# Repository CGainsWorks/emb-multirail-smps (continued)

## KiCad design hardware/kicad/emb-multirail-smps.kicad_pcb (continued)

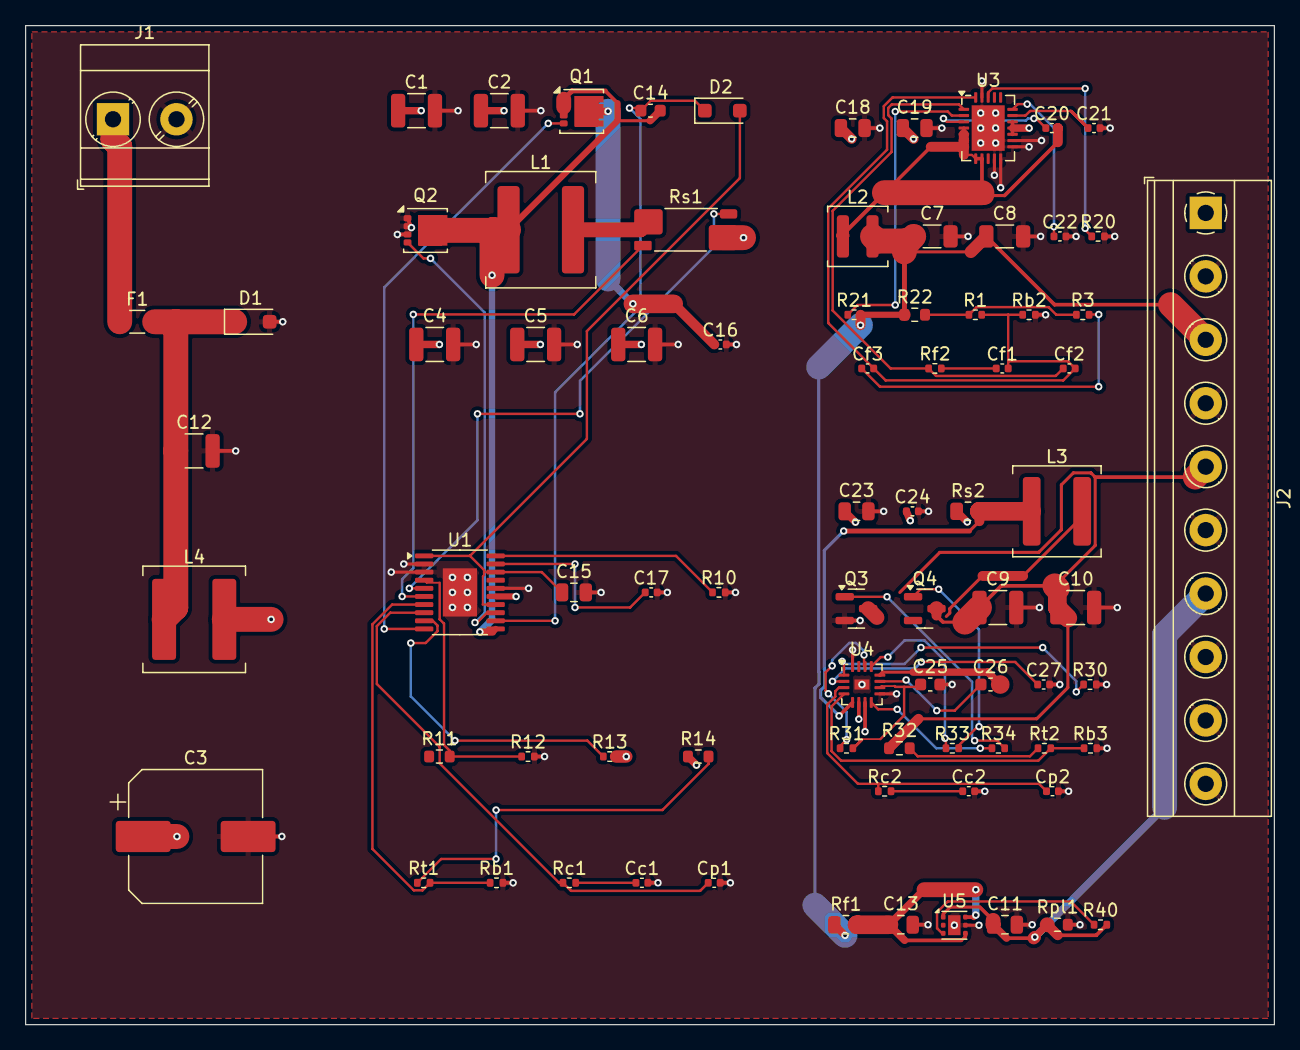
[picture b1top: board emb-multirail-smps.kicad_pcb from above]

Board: 4 copper layers, 100.0 x 80.0 mm, 79 parts (0 on the bottom side), 52 nets.

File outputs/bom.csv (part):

refs,qty,value,description,footprint,manufacturer,mpn,basis,status
J1,1,VIN 8-36V,"Input terminal block, 2 way, 5.08 mm",TerminalBlock_Phoenix:TerminalBlock_Phoenix_MKDS-3-2-5.08_1x02_P5.08mm_Horizontal,Phoenix Contact,1711725,choice,"selected, data sheet check pending"
F1,1,3A,"Fuse, 3 A slow blow, 63 V DC, 1206",Fuse:Fuse_1206_3216Metric,Eaton Bussmann,CC12H3A-TR,choice,"selected, data sheet check pending"
D1,1,SMF36A,"TVS, 36 V stand off, unidirectional, SOD-123FL. Clamps input transients and conducts on reverse polarity until F1 opens",Diode_SMD:D_SOD-123F,Littelfuse,SMF36A,choice,"selected, data sheet check pending"
C12,1,2.2uF,"Input filter shunt capacitor, connector side, 2.2 uF 100 V X7R",Capacitor_SMD:C_1210_3225Metric,Murata,GRM32ER72A225KA35L,model,"selected, data sheet check pending"
L4,1,10uH,"Differential mode input filter inductor, 10 uH",Inductor_SMD:L_Coilcraft_XAL7050-XXX,Coilcraft,XAL7050-103MEC,model,"selected, data sheet check pending"
C3,1,220uF,"Hybrid polymer aluminium 220 uF 50 V, 10 x 16.5 mm, input filter damping",Capacitor_SMD:CP_Elec_10x10.5,Panasonic,EEH-ZS1H221P,model,"selected, data sheet check pending"
C1 C2,2,10uF,"+5V buck input capacitor, 10 uF 50 V X7R 1210",Capacitor_SMD:C_1210_3225Metric,Murata,GRM32ER71H106KA12L,model,"selected, data sheet check pending"
U1,1,LTC3891EFE#PBF,"60 V synchronous buck controller, peak current mode, 0.8 V reference",Package_SO:HTSSOP-20-1EP_4.4x6.5mm_P0.65mm_EP2.74x3.86mm,Analog Devices,LTC3891EFE#PBF,datasheet,"selected, data sheet check pending"
Q1 Q2,2,CSD18543Q3A,"60 V N-channel MOSFET, high side",Package_SON:VSON-8_3.3x3.3mm_P0.65mm_NexFET,Texas Instruments,CSD18543Q3A,choice,"selected, data sheet check pending"
D2,1,PMEG6010CEH,"Bootstrap diode, 60 V Schottky. The data sheet calls for one between INTVCC and BOOST",Diode_SMD:D_SOD-123F,Nexperia,PMEG6010CEH,datasheet,"selected, data sheet check pending"
C14 C26,2,100nF,"Bootstrap capacitor, 0.1 uF 50 V",Capacitor_SMD:C_0603_1608Metric,Murata,GRM188R71H104KA93D,datasheet,"selected, data sheet check pending"
C15,1,4.7uF,INTVCC decoupling. Data sheet minimum 2.2 uF,Capacitor_SMD:C_0805_2012Metric,Murata,GRM21BR71C475KA73L,datasheet,"selected, data sheet check pending"
C16 C21 C24 Cc2,4,100nF,VIN pin bypass to SGND,Capacitor_SMD:C_0402_1005Metric,Murata,GRM155R71H104KE14D,datasheet,"selected, data sheet check pending"
C17 C20 C27,3,47nF,Soft start. tSS = CSS * 0.8 V / 10 uA = 3.8 ms,Capacitor_SMD:C_0402_1005Metric,Murata,GRM155R71C473KA01D,datasheet,"selected, data sheet check pending"
R10,1,71.5k,"Frequency set, 500 kHz",Resistor_SMD:R_0402_1005Metric,Yageo,RC0402FR-0771K5L,datasheet,"selected, data sheet check pending"
R11,1,1M,RUN divider top. Starts at about 7 V rising,Resistor_SMD:R_0603_1608Metric,Yageo,RC0603FR-071ML,datasheet,"selected, data sheet check pending"
R12,1,210k,"RUN divider bottom. 1.21 V threshold, 6.3 V at 36 V in",Resistor_SMD:R_0402_1005Metric,Yageo,RC0402FR-07210KL,datasheet,"selected, data sheet check pending"
R13 R21 R40,3,100k,PGOOD pull-up,Resistor_SMD:R_0402_1005Metric,Yageo,RC0402FR-07100KL,choice,"selected, data sheet check pending"
L1,1,6.8uH,"+5V buck inductor, 6.8 uH",Inductor_SMD:L_Coilcraft_XAL8080-XXX,Coilcraft,XAL8080-682MED,model,"selected, data sheet check pending"
Rs1,1,5m,"Current sense shunt, 5 mOhm 1 %, four terminal 2512",Resistor_SMD:R_Shunt_Vishay_WSK2512_6332Metric_T1.19mm,Vishay,WSK25125L000FEA,model,"selected, data sheet check pending"
C4 C5 C6 C9 C10,5,22uF,"+5V output capacitor, 22 uF 25 V X7R 1210",Capacitor_SMD:C_1210_3225Metric,Murata,GRM32ER71E226KE15L,model,"selected, data sheet check pending"
R14 R22 R32,3,0,Loop injection link. Fitted 0 ohm; replace with 20 ohm for a Bode measurement,Resistor_SMD:R_0603_1608Metric,Yageo,RC0603JR-070RL,choice,"selected, data sheet check pending"
Rt1,1,26.1k,+5V divider top,Resistor_SMD:R_0402_1005Metric,Yageo,RC0402FR-0726K1L,model,"selected, data sheet check pending"
Rb1 Rb3,2,4.99k,+5V divider bottom,Resistor_SMD:R_0402_1005Metric,Yageo,RC0402FR-074K99L,model,"selected, data sheet check pending"
Rc1,1,2.4k,"+5V Type II, Rc",Resistor_SMD:R_0402_1005Metric,Yageo,RC0402FR-072K4L,model,"selected, data sheet check pending"
Cc1,1,15nF,"+5V Type II, Cc",Capacitor_SMD:C_0402_1005Metric,Murata,GRM155R71H153KA12D,model,"selected, data sheet check pending"
Cp1 Cp2,2,270pF,"+5V Type II, Cp",Capacitor_SMD:C_0402_1005Metric,KEMET,C0402C271J5GACTU,model,"selected, data sheet check pending"
U3,1,TPS54317RHFR,"3 to 6 V input, 3 A synchronous buck, voltage mode, integrated FETs, 0.891 V reference",Package_DFN_QFN:QFN-24-1EP_4x5mm_P0.5mm_EP2.65x3.65mm,Texas Instruments,TPS54317RHFR,datasheet,"selected, data sheet check pending"
C18 C19 C23 C13,4,10uF,"+3V3 buck input capacitor, 10 uF 16 V X7R 0805",Capacitor_SMD:C_0805_2012Metric,Samsung,CL21B106KOQNNNE,model,"selected, data sheet check pending"
C22,1,22nF,Slow start. t = C * 0.7 V / 5 uA = 3.1 ms,Capacitor_SMD:C_0402_1005Metric,Murata,GRM155R71H223KA12D,datasheet,"selected, data sheet check pending"
R20,1,46.4k,"Frequency set, 1 MHz. f(MHz) = 51k / (R + 4.7k) gives 46.3k",Resistor_SMD:R_0402_1005Metric,Yageo,RC0402FR-0746K4L,datasheet,"selected, data sheet check pending"
L2,1,1.5uH,"+3V3 buck inductor, 1.5 uH",Inductor_SMD:L_Coilcraft_XAL4020-XXX,Coilcraft,XGL4020-152MEC,model,"selected, data sheet check pending"
C7 C8,2,22uF,"+3V3 output capacitor, 22 uF 16 V X7R 1206",Capacitor_SMD:C_1206_3216Metric,Murata,GRM31CZ71C226ME15L,model,"selected, data sheet check pending"
R1,1,10.2k,"+3V3 Type III R1, also the divider top",Resistor_SMD:R_0402_1005Metric,Yageo,RC0402FR-0710K2L,model,"selected, data sheet check pending"
Rb2,1,3.74k,+3V3 divider bottom,Resistor_SMD:R_0402_1005Metric,Yageo,RC0402FR-073K74L,model,"selected, data sheet check pending"
R3,1,115,+3V3 Type III R3,Resistor_SMD:R_0402_1005Metric,Yageo,RC0402FR-07115RL,model,"selected, data sheet check pending"
Cf3,1,1.3nF,+3V3 Type III Cf3,Capacitor_SMD:C_0402_1005Metric,KEMET,C0402C132J5GACTU,model,"selected, data sheet check pending"
Rf2,1,4.42k,+3V3 Type III Rf,Resistor_SMD:R_0402_1005Metric,Yageo,RC0402FR-074K42L,model,"selected, data sheet check pending"
Cf1,1,3.3nF,+3V3 Type III Cf1,Capacitor_SMD:C_0402_1005Metric,Murata,GRM1555C1H332JE01D,model,"selected, data sheet check pending"
Cf2,1,75pF,+3V3 Type III Cf2,Capacitor_SMD:C_0402_1005Metric,KEMET,C0402C750J5GACTU,model,"selected, data sheet check pending"
U4,1,TPS43061RTER,"Synchronous boost controller, peak current mode, 5.5 V gate drive, integrated bootstrap diode, 1.22 V reference",Package_DFN_QFN:Texas_RTE_WQFN-16-1EP_3x3mm_P0.5mm_EP1.2x0.8mm,Texas Instruments,TPS43061RTER,datasheet,"selected, data sheet check pending"
R33 R34,2,0,"High side gate resistor. Fitted 0 ohm, there to slow the edge if the switch node rings on the real board",Resistor_SMD:R_0402_1005Metric,Yageo,RC0402JR-070RL,choice,"selected, data sheet check pending"
C25,1,1uF,VCC decoupling. Data sheet range 0.47 to 10 uF,Capacitor_SMD:C_0603_1608Metric,Murata,GRM188R71C105KA12D,datasheet,"selected, data sheet check pending"
R30,1,147k,"Frequency set, 400 kHz",Resistor_SMD:R_0402_1005Metric,Yageo,RC0402FR-07147KL,datasheet,"selected, data sheet check pending"
R31,1,10k,"PGOOD pull-up to VCC, 10k as the data sheet recommends",Resistor_SMD:R_0402_1005Metric,Yageo,RC0402FR-0710KL,datasheet,"selected, data sheet check pending"
Rs2,1,50m,"Current sense shunt, 50 mOhm 1 %, in series with the inductor",Resistor_SMD:R_0805_2012Metric,Vishay,WSLP0805R0500FEA,model,"selected, data sheet check pending"
L3,1,22uH,"+12V boost inductor, 22 uH",Inductor_SMD:L_Coilcraft_XAL6060-XXX,Coilcraft,XGL6060-223MEC,model,"selected, data sheet check pending"
Q3 Q4,2,AO3400A,"30 V N-channel MOSFET, boost low side",Package_TO_SOT_SMD:SOT-23,Alpha and Omega,AO3400A,choice,"selected, data sheet check pending"
Rt2,1,44.2k,+12V divider top,Resistor_SMD:R_0402_1005Metric,Yageo,RC0402FR-0744K2L,model,"selected, data sheet check pending"
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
